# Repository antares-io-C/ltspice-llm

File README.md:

<h1 align="center">
  <picture>
    <source media="(prefers-color-scheme: dark)" srcset="docs/assets/logo-dark.svg">
    
  </picture>
</h1>

<p align="center"><a href="README.tr.md">Türkçe</a> · <b>English</b></p>

<p align="center"><b>Let your language model run LTspice.</b></p>

[LTspice](https://www.analog.com/en/resources/design-tools-and-calculators/ltspice-simulator.html) is Analog Devices'
free circuit simulator; it is built for a graphical interface, and its `.log`/`.raw` output is too large and raw for a
language model to read. **ltspice-llm** runs it in the background, reads the `.meas` measurements, the operating point
and the errors, and turns each waveform into a short JSON summary (min, max, mean, RMS and a 15-point trend). With the
ready-made tool schemas a model can build a circuit, simulate it, read the numbers and change values; the library
itself does not contact any model provider.

```text
LLM or Python ──(circuit)──► ltspice-llm ──► LTspice (in the background)
        ▲                                          │
        └──────── short summary (JSON) ◄───────────┘
```

## What you can do

- **Simulate a netlist and get the numbers back.** LTspice runs headless; `.meas` results, the operating point and
  errors come back as a Python dict. [examples/01_basic_simulation.py](examples/01_basic_simulation.py)
- **Plot waveforms.** Save `.tran` traces as PNG; the plotting tools can also return the image as Base64 for
  multimodal models. [examples/02_waveform_plotting.py](examples/02_waveform_plotting.py)
- **Give a model LTspice as tools.** 10 tool schemas in OpenAI, Anthropic, Gemini or generic format;
  `handle_tool_call` runs the model's tool calls. [examples/03_llm_function_calling_demo.py](examples/03_llm_function_calling_demo.py)
- **Run the tool loop without writing it.** `AutonomousCircuitAgent` calls your model function, runs the tools it asks
  for and stops when the model stops calling tools. The example plays the model from a script, so it needs no API key.
  [examples/08_agent_loop_with_scripted_llm.py](examples/08_agent_loop_with_scripted_llm.py)
- **Tune a value to a target.** Bisection on one parameter until a `.meas` result is within tolerance of the target.
  [examples/04_closed_loop_tuning.py](examples/04_closed_loop_tuning.py)
- **Follow a filter design through the tools.** A 10 kHz Sallen-Key low-pass: AC analysis with the −3 dB point, Bode
  plot, step response. The tool calls are scripted.
  [examples/05_filter_design_walkthrough.py](examples/05_filter_design_walkthrough.py)
- **Round to standard values, sweep temperature, diagnose a failure.** E24 rounding, a `.step temp` sweep with
  min/max/mean/std per measurement, and a diagnosis of a deliberately broken circuit.
  [examples/07_quantization_sweep_and_diagnosis.py](examples/07_quantization_sweep_and_diagnosis.py)
- **Sweep and run in parallel.** `run_sweep` runs a parameter sweep as a single LTspice `.step` run; `run_batch` runs
  independent circuits at the same time and caps the solver threads so the instances do not livelock.
  [examples/10_performance_fast_paths.py](examples/10_performance_fast_paths.py)
- **Check a formula against LTspice and write a report.** A single-file HTML report with waveforms, measurement tables
  and reliability checks. [examples/15_hotplug_damping_validation.py](examples/15_hotplug_damping_validation.py)
- **Compare two runs and export waveforms.** `compare_circuits` tells which netlist variables differ between two
  simulated circuits and gives the before/after difference of their `.meas` results; `export_waveforms_csv` writes
  `.raw` traces to CSV for Excel, MATLAB or pandas. Both are in the extended tool set (`include_extended=True`).
  [docs/GUIDE.md](docs/GUIDE.md#comparing-two-circuits)
- **Check the phase and gain margin of a feedback loop.** Break the loop with an AC source (Middlebrook injection) and
  run `.ac`; `raw_loop_margins` gives the gain crossover, phase margin and gain margin for each step and lists every
  crossing. The `analyze_loop_stability` tool lets a model do the same (extended set). Tested against an LTspice run of
  a three-pole loop whose margins are known in closed form. The example measures how a capacitive load lowers the
  phase margin of an op-amp follower and how an isolation resistor restores it.
  [examples/22_loop_stability_capacitive_load.py](examples/22_loop_stability_capacitive_load.py),
  [docs/GUIDE.md](docs/GUIDE.md#phase-and-gain-margin-of-a-feedback-loop)
- **Check results against specs.** Write the limits down and let the code decide: `verify_specs` compares a
  simulated circuit's `.meas` results with `min`/`max` limits and returns PASS, FAIL or UNVERIFIED per
  measurement, with the margin to the nearest limit. Every step of a stepped run is checked, and a measurement
  LTspice could not compute is never a pass. Each limit can carry an uncertainty, used as a guard band
  (JCGM 106), and a source; `numerical_check` reruns the circuit with tighter solver settings and adds the
  change to the guard band. A stepped corner run names the `.step` values of the worst step, and `model_specs`
  checks the model against its datasheet first: if it fails, a design pass becomes UNVERIFIED.
  [docs/GUIDE.md](docs/GUIDE.md#checking-results-against-specs)
- **Read trace lengths from a KiCad board.** `read_kicad_board` reads a `.kicad_pcb` file without KiCad, finds the
  shortest trace path between two pads and turns it into an R/L/C model for the netlist, with the dielectric and
  copper thickness taken from the board's stackup; the `read_board_trace` tool lets a model do the same. The reader
  only reads the board file and was checked against KiCad's own computation. The end-to-end example puts the path into
  a supply circuit and measures its DC drop and the dip at a load step in LTspice.
  [examples/21_board_trace_to_simulation.py](examples/21_board_trace_to_simulation.py),
  [docs/GUIDE.md](docs/GUIDE.md#reading-a-trace-path-from-a-kicad-board)
- **Turn results into slides and animated GIFs.** Two agent skills build an editable `.pptx` deck and looping waveform
  GIFs from simulation results; the end-to-end example runs LTspice and produces the report, two GIFs and a deck.
  [examples/19_simulation_to_slides.py](examples/19_simulation_to_slides.py),
  [agent skills](#agent-skills-slides-and-animated-gifs)

Also included: reading, editing and generating `.asc` schematics and finding unconnected pins
(see [docs/GUIDE.md](docs/GUIDE.md)).

## ltspice-llm or LTspice's own MCP server?

Since version 26.1.0 (August 2026) LTspice ships its own MCP server, `ltspice-mcp-bridge.exe`. It connects an AI
assistant such as Claude Code, Claude Desktop, Cursor or GitHub Copilot to the schematic you have open in LTspice: the
assistant reads and edits it, runs the simulation and reads the results while you watch, and on Windows LTspice can
set these tools up for you (*Tools > Configure Third-Party AI Assistants*; LTspice Help, "Third Party AI Tools"). If
you want to talk to an assistant about the design on your screen, use that.

ltspice-llm is for programs that drive LTspice without a window:

- Python scripts and CI jobs: parameter sweeps and parallel runs that cap the solver threads so instances do not
  livelock, closed-loop tuning, E-series rounding, convergence diagnosis and HTML reports.
- Your own agent on a model API (Anthropic, OpenAI, Gemini, or a local model), with short JSON summaries of each run
  instead of raw `.log` and `.raw` files.

## Quick start

You need Windows, Python 3.10 or newer, and LTspice installed separately
([download from Analog Devices](https://www.analog.com/en/resources/design-tools-and-calculators/ltspice-simulator.html)).

```bash
git clone https://github.com/antares-io-C/ltspice-llm.git
cd ltspice-llm
pip install -e .
```

Simulate an RC low-pass filter and read its measurements:

```python
from ltspice_llm import LTSpiceAdapter

netlist = """* RC low-pass filter
V1 in 0 PULSE(0 5 0 1n 1n 1m 2m)
R1 in out 1k
C1 out 0 1u
.tran 5m
.meas tran v_max MAX V(out)
.meas tran v_tau FIND V(out) WHEN time=1m
.end
"""

result = LTSpiceAdapter().run_netlist(netlist, circuit_name="rc_filter")
print(result.success)        # True
print(result.measurements)   # {'v_max': 3.64623451233, 'v_tau': 3.16060549511, 'v_tau_at': 0.001}
print(result.to_llm_dict())  # the short summary you pass to a model
```

`v_tau` is the output one time constant (RC = 1 ms) after the step: 5 V × (1 − 1/e) ≈ 3.16 V.

To see a model use the tools, run the agent loop with a scripted model (no API key needed):

```bash
python examples/08_agent_loop_with_scripted_llm.py
```

LTspice is found in its usual install locations; if yours is elsewhere, set `LTSPICE_EXE` to its path. The examples
print their progress in Turkish.

### Your own schematic or netlist

```python
result = LTSpiceAdapter().run_netlist(r"C:\designs\buck\buck.asc", circuit_name="buck")
```

A circuit given as a file path runs in its own folder, as it does in the LTspice GUI, so the model files next to it
(relative `.include` and `.lib`) and your own symbols are found. During the run a temporary
`_ltspice_llm_*` copy sits in that folder; afterwards the copy and the results move to the adapter's workspace, and
your file is not changed.

## Using it with an AI model

```python
from ltspice_llm import get_ltspice_tool_schemas, handle_tool_call

tools = get_ltspice_tool_schemas("anthropic")   # "openai" | "anthropic" | "gemini" | "generic"

# Give the tools to the model. When the model calls a tool, pass on its name and arguments:
result = handle_tool_call("create_or_replace_circuit",
                          {"circuit_name": "rc_filter", "netlist_code": netlist})
# result is a dict; serialize it to JSON and return it to the model as the tool result.
```

If you would rather not write the loop yourself, `AutonomousCircuitAgent` calls your model, runs the tools it asks
for and keeps going until the model is done. It does not connect to any provider and reads no API keys; you pass the
model in as a function. A complete loop with Claude (`pip install anthropic`, then set `ANTHROPIC_API_KEY`):

```python
import anthropic

from ltspice_llm import CIRCUIT_DESIGNER_SYSTEM_PROMPT_EN, AutonomousCircuitAgent, get_ltspice_tool_schemas
from ltspice_llm.providers import from_anthropic, to_anthropic

client = anthropic.Anthropic()
tools = get_ltspice_tool_schemas("anthropic")  # built once: the tool list must not change during a conversation

def llm(history, _tools):
    system, messages = to_anthropic(history)
    response = client.beta.messages.create(
        model="claude-opus-5-5",
        max_tokens=16000,
        output_config={"effort": "high"},
        betas=["server-side-fallback-2026-07-01"],
        fallbacks="default",  # if Claude declines the request, the API retries it on another Claude model
        system=system,
        tools=tools,
        messages=messages,
    )
    if response.stop_reason == "refusal":
        raise RuntimeError(f"Claude declined the request: {response.stop_details}")
    return from_anthropic(response)

agent = AutonomousCircuitAgent(system_prompt=CIRCUIT_DESIGNER_SYSTEM_PROMPT_EN)
outcome = agent.run("Design an RC low-pass filter with a 1 kHz cutoff and check the -3 dB point in LTspice.", llm)
print(outcome["final_message"])
```

`from_anthropic` keeps Claude's thinking blocks, and `to_anthropic` sends every earlier turn back unchanged: current
Claude models tie their thinking to the conversation, and an edited history loses it or is rejected. The same module
has converters for OpenAI (`to_openai`, `from_openai`) and Gemini (`to_gemini`, `from_gemini`). To try the loop without
an API key, run [examples/08_agent_loop_with_scripted_llm.py](examples/08_agent_loop_with_scripted_llm.py), which
plays the model from a script.

The tool descriptions and the messages in tool results are in Turkish, and so is the agent's default system prompt.
`system_prompt=CIRCUIT_DESIGNER_SYSTEM_PROMPT_EN` gives the agent the English translation of that prompt.

## Examples

All 15 runnable examples are in [examples/](examples/). There is also an interactive terminal interface:
`python interactive_designer.py`. The code comments and the detailed documentation are in Turkish.

## Agent skills: slides and animated GIFs

Two [Agent Skills](https://agentskills.io/specification) turn simulation results into material for other people.
Their scripts don't import `ltspice_llm`; they need `pip install -e ".[media]"` (python-pptx, Pillow).

- [narrative-pptx](.agents/skills/narrative-pptx/SKILL.md): an editable `.pptx` deck from a JSON story spec
  (assertion headlines, seven layouts, annotated charts, speaker notes), plus a geometry and visual check.
  `python .agents/skills/narrative-pptx/scripts/deck_builder.py .agents/skills/narrative-pptx/assets/example_spec.json -o deck.pptx`
  builds the sample deck.
- [explainer-gif](.agents/skills/explainer-gif/SKILL.md): looping GIFs from waveforms or parameter sweeps that stay
  readable in a slide (poster frame, slow motion at edges, latched callouts, minimum text time), plus a validator.

[examples/19_simulation_to_slides.py](examples/19_simulation_to_slides.py) runs LTspice and produces the report,
two GIFs and a deck end to end. A third skill, [verify-review](.agents/skills/verify-review/SKILL.md), checks an AI
review's claims against LTspice measurements before applying them.

The skills live in `.agents/skills/`, where Antigravity and other Agent Skills clients find them. Claude Code reads
only `.claude/skills/`, so each skill has a short pointer file there with the same name and description;
`tests/test_skills.py` keeps the two in step. The skill instructions are in Turkish.

## Project layout

```text
ltspice_llm/      the library: LTspice adapter, output parsers, LLM tools, diagnosis, reports
examples/         runnable examples
docs/             detailed user guide and measurement-backed lessons (Turkish)
tests/            tests (most of them run without LTspice)
scripts/          quality gate and test tooling
.agents/skills/   agent skills: slide decks and animated GIFs
```

## Tests

```bash
pip install -e ".[dev]"
python scripts/check.py          # lint + the tests that don't need LTspice
python scripts/check.py --full   # tests and examples against a real LTspice
```

## Limitations

- Simulations have only been run on Windows with LTspice 26.1.1. The code also looks for LTspice on macOS and accepts
  a Wine wrapper on Linux through `LTSPICE_EXE`, but neither has been tested. CI runs only the tests that do not need
  LTspice (Ubuntu and Windows; Python 3.10, 3.12 and 3.14).
- The tool layer (`handle_tool_call`, `AutonomousCircuitAgent`) rejects directives in a language model's netlist
  that write files (`.wave`, `.savebias`, `savestate`) and paths that reach outside the workspace (absolute paths,
  `..`, environment variables such as `%USERPROFILE%`); library names (`.lib standard.dio`) are allowed. If the input is trusted, pass `allow_file_access=True`.
  Code that calls `LTSpiceAdapter.run_netlist` directly is not checked. The model's netlists run in the adapter's
  workspace (by default `ltspice_llm_runs` in the temp folder); to let the model use a vendor model file, put the file
  in a folder and pass `adapter=LTSpiceAdapter(workspace_dir=that_folder)` to `handle_tool_call` or
  `AutonomousCircuitAgent`.
- The provider schema formats are generated from the providers' documentation; they are not tested automatically
  against the live APIs.

## More

- [docs/GUIDE.md](docs/GUIDE.md): every feature, API details, performance measurements, the livelock
  guard and the full list of known limitations (Turkish original: [docs/KILAVUZ.md](docs/KILAVUZ.md))
- [docs/](docs/) (Turkish): measurement-backed lessons on LTspice and performance
- [CHANGELOG.md](CHANGELOG.md): release history
- [CONTRIBUTING.md](CONTRIBUTING.md): how to contribute

## License

GPL-3.0-or-later; the full text is in [LICENSE](LICENSE). Copyright © 2026 ltspice-llm contributors.

LTspice is a registered trademark of Analog Devices, Inc. This project is not affiliated with or endorsed by Analog
Devices. You need to install LTspice yourself; this repository does not distribute it.

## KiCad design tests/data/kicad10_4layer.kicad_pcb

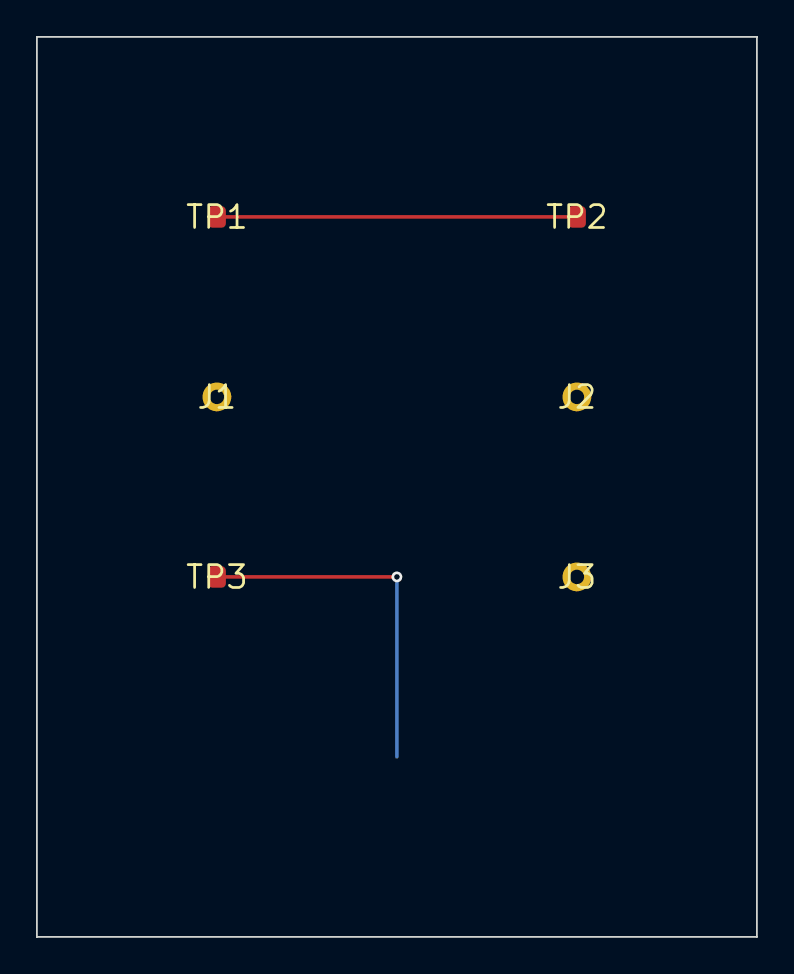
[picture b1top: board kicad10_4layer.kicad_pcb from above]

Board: 4 copper layers, 40.0 x 50.0 mm, 7 parts (1 on the bottom side), 3 nets.

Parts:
J1: J1
J2: J2
J3: J3
TP1: TP1
TP2: TP2
TP3: TP3
TP4: TP4

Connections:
/BLIND: J3.1, TP3.1, TP4.1
/INNER: J1.1, J2.1
/OUTER: TP1.1, TP2.1

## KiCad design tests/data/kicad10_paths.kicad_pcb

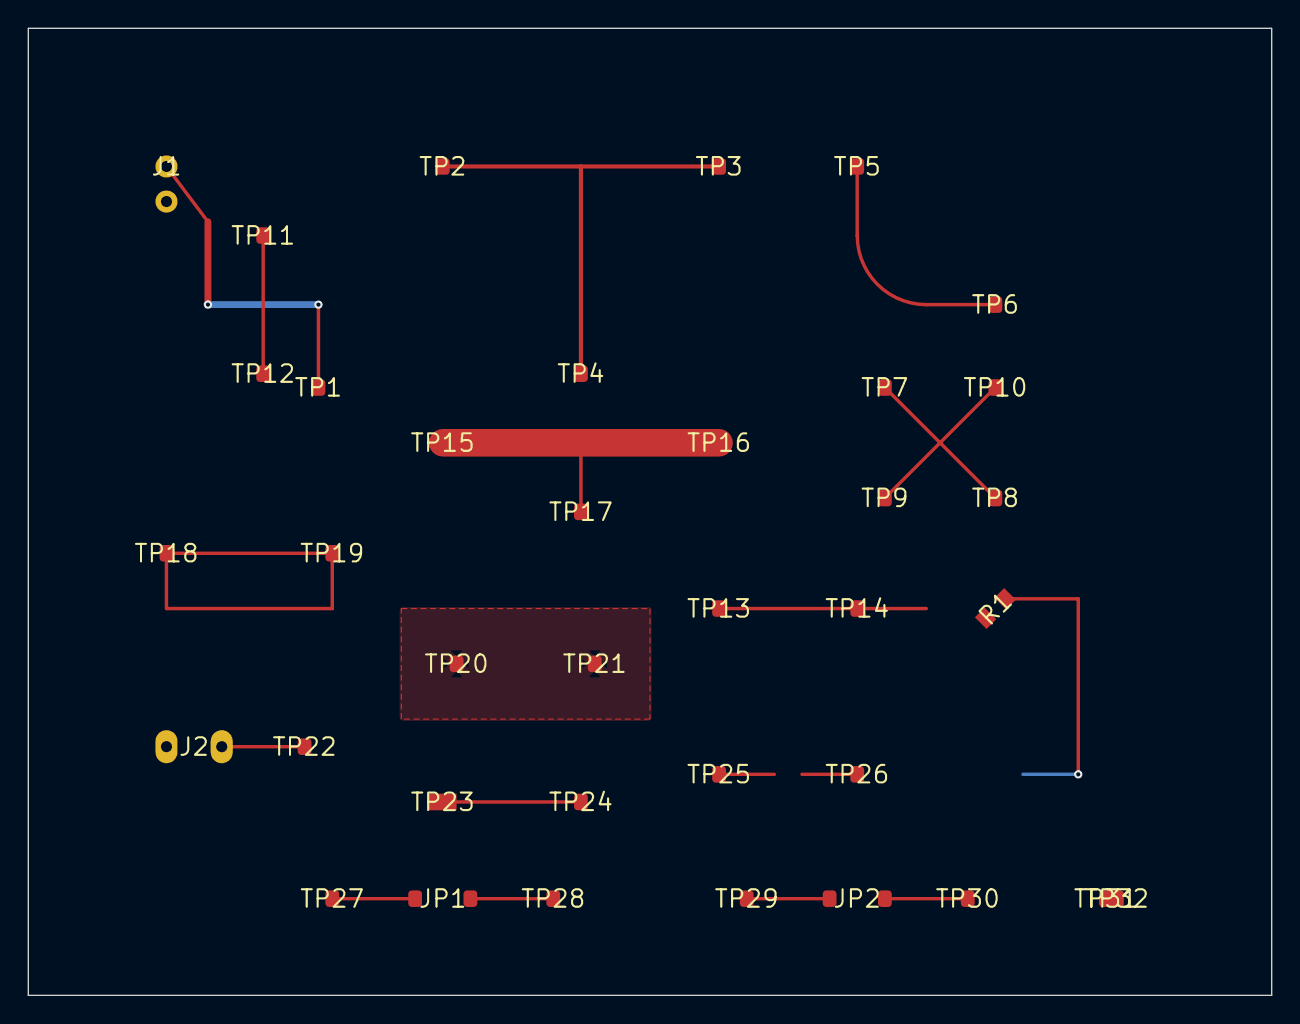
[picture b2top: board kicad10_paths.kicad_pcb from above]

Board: 2 copper layers, 90.0 x 70.0 mm, 38 parts (1 on the bottom side), 16 nets.

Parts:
C1: C1
J1: J1
J2: J2
JP1: JP1
JP2: JP2
R1: R1
TP1: TP1
TP2: TP2
TP3: TP3
TP4: TP4
TP5: TP5
TP6: TP6
TP7: TP7
TP8: TP8
TP9: TP9
TP10: TP10
TP11: TP11
TP12: TP12
TP13: TP13
TP14: TP14
TP15: TP15
TP16: TP16
TP17: TP17
TP18: TP18
TP19: TP19
TP20: TP20
TP21: TP21
TP22: TP22
TP23: TP23
TP24: TP24
TP25: TP25
TP26: TP26
TP27: TP27
TP28: TP28
TP29: TP29
TP30: TP30
TP31: TP31
TP32: TP32

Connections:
/ARC: TP5.1, TP6.1
/CHAIN: J1.1, TP1.1
/CROSS: TP7.1, TP8.1, TP9.1, TP10.1
/GAP: TP25.1, TP26.1
/JGRP: JP2.1, JP2.2, TP29.1, TP30.1
/JMP: JP1.1, TP27.1, TP28.1
/LOOP: TP18.1, TP19.1
/OFFC: TP23.1, TP24.1
/POUR: TP20.1, TP21.1
/ROT: C1.1, R1.2
/SHLD: J2.S, TP22.1
/STUB: TP13.1, TP14.1
/TEE: TP2.1, TP3.1, TP4.1
/TOUCH: TP31.1, TP32.1
/WIDE: TP15.1, TP16.1, TP17.1
/XSLOT: TP11.1, TP12.1
